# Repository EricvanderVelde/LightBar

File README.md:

# LightBar
N-Scale model train internal lighting

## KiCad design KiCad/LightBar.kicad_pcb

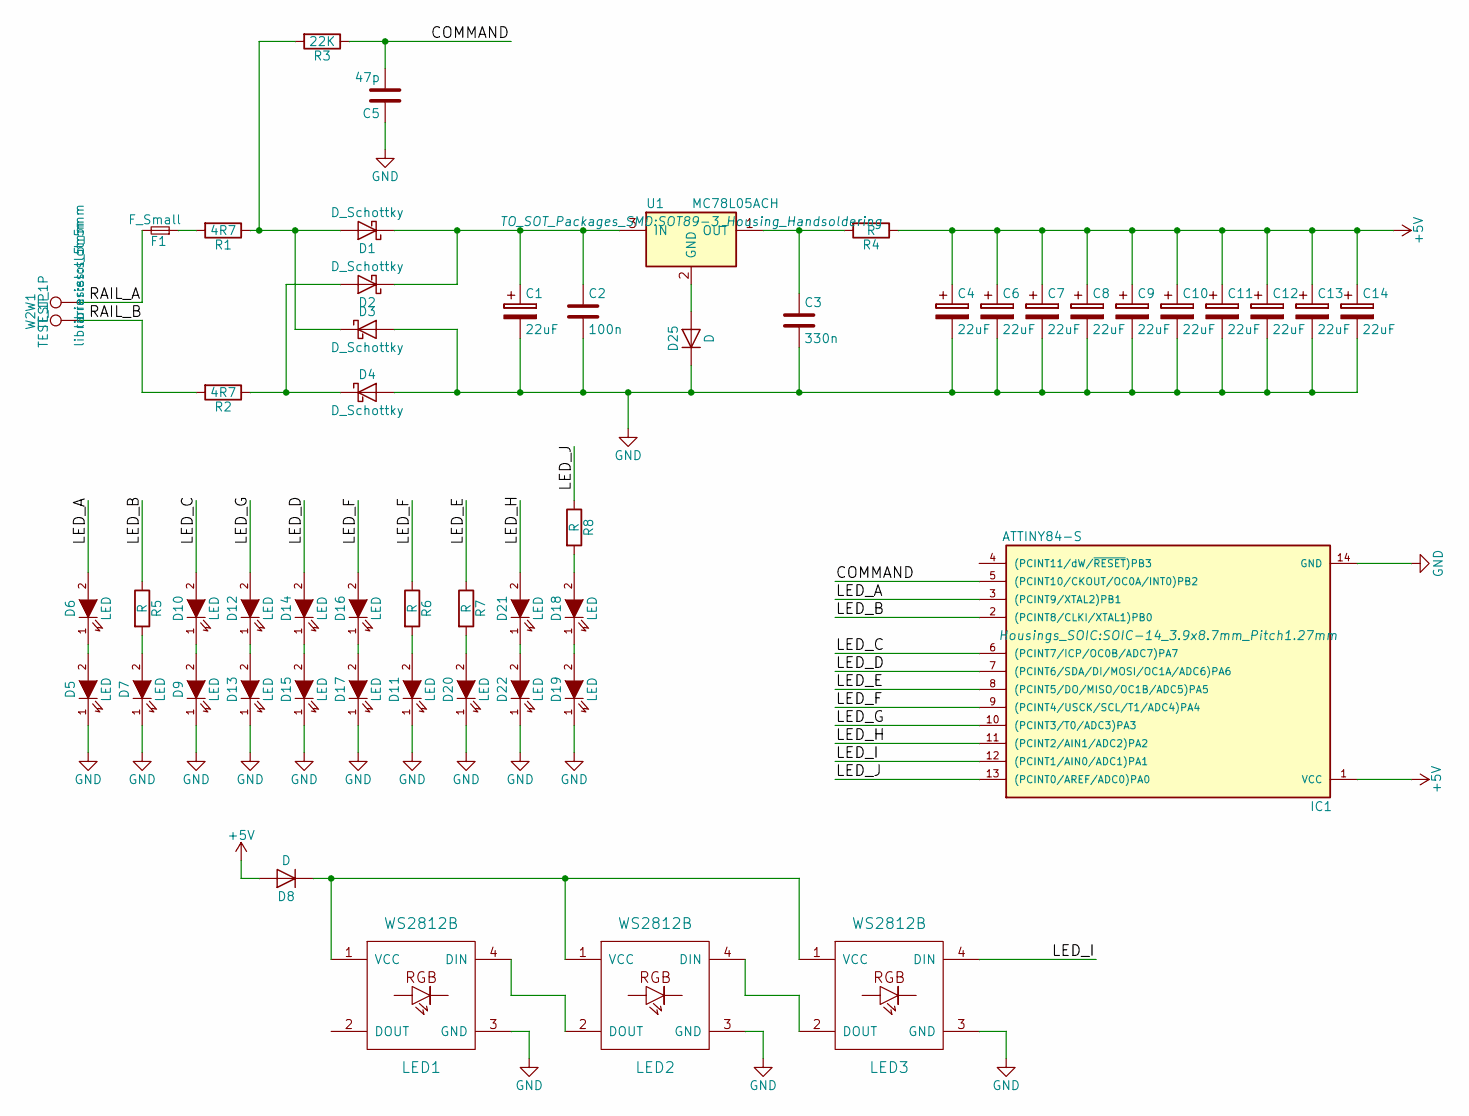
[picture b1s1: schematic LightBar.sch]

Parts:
C1, C4, C6, C7, C8, C9, C10, C11, C12, C13, C14: 22uF; TantalC_SizeB_EIA-3528_HandSoldering
C2: 100n; C_0805_HandSoldering
C3: 330n; C_0805_HandSoldering
C5: 47p; C_0805_HandSoldering
D1, D2, D3, D4: D_Schottky; SOD-323
D5, D6, D7, D9, D10, D11, D12, D13, D14, D15, D16, D17, D18, D19, D20, D21, D22: LED; LED_0805
D8, D25: D; SOD-323
F1: F_Small; R_0805_HandSoldering
IC1: ATTINY84-S; SOIC-14_3.9x8.7mm_Pitch1.27mm
LED1, LED2, LED3: WS2812B
R1, R2: 4R7; R_0805_HandSoldering
R3: 22K; R_0805_HandSoldering
R4, R5, R6, R7, R8: R; R_0805_HandSoldering
U1: MC78L05ACH; SOT89-3_Housing_Handsoldering
W1, W2: TEST_1P; slot_5mm

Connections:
+5V: C4.1, C6.1, C7.1, C8.1, C9.1, C10.1, C11.1, C12.1, C13.1, C14.1, D8.2 (A), IC1.1 (VCC), R4.1
/COMMAND: C5.2, IC1.5 ((PCINT10/CKOUT/OC0A/INT0)PB2), R3.1
/LED_A: D6.2 (A), IC1.3 ((PCINT9/XTAL2)PB1)
/LED_B: IC1.2 ((PCINT8/CLKI/XTAL1)PB0), R5.1
/LED_C: D10.2 (A), IC1.6 ((PCINT7/ICP/OC0B/ADC7)PA7)
/LED_D: D14.2 (A), IC1.7 ((PCINT6/SDA/DI/MOSI/OC1A/ADC6)PA6)
/LED_E: IC1.8 ((PCINT5/DO/MISO/OC1B/ADC5)PA5), R7.1
/LED_F: D16.2 (A), IC1.9 ((PCINT4/USCK/SCL/T1/ADC4)PA4), R6.1
/LED_G: D12.2 (A), IC1.10 ((PCINT3/T0/ADC3)PA3)
/LED_H: D21.2 (A), IC1.11 ((PCINT2/AIN1/ADC2)PA2)
/LED_I: IC1.12 ((PCINT1/AIN0/ADC1)PA1), LED3.4 (DIN)
/LED_J: IC1.13 ((PCINT0/AREF/ADC0)PA0), R8.1
/RAIL_A: F1.2, W1.1
/RAIL_B: R2.2, W2.1
GND: C1.2, C2.2, C3.2, C4.2, C5.1, C6.2, C7.2, C8.2, C9.2, C10.2, C11.2, C12.2, C13.2, C14.2, D3.2 (A), D4.2 (A), D5.1 (K), D7.1 (K), D9.1 (K), D11.1 (K), D13.1 (K), D15.1 (K), D17.1 (K), D19.1 (K), D20.1 (K), D22.1 (K), D25.1 (K), IC1.14 (GND), LED1.3 (GND), LED2.3 (GND), LED3.3 (GND)
unnamed: C1.1, C2.1, D1.1 (K), D2.1 (K), U1.3 (IN)
unnamed: C3.1, R4.2, U1.1 (OUT)
unnamed: D1.2 (A), D3.1 (K), R1.1, R3.2
unnamed: D2.2 (A), D4.1 (K), R2.1
unnamed: D5.2 (A), D6.1 (K)
unnamed: D7.2 (A), R5.2
unnamed: D8.1 (K), LED1.1 (VCC), LED2.1 (VCC), LED3.1 (VCC)
unnamed: D9.2 (A), D10.1 (K)
unnamed: D11.2 (A), R6.2
unnamed: D12.1 (K), D13.2 (A)
unnamed: D14.1 (K), D15.2 (A)
unnamed: D16.1 (K), D17.2 (A)
unnamed: D18.1 (K), D19.2 (A)
unnamed: D18.2 (A), R8.2
unnamed: D20.2 (A), R7.2
unnamed: D21.1 (K), D22.2 (A)
unnamed: D25.2 (A), U1.2 (GND)
unnamed: F1.1, R1.2
unnamed: LED1.4 (DIN), LED2.2 (DOUT)
unnamed: LED2.4 (DIN), LED3.2 (DOUT)

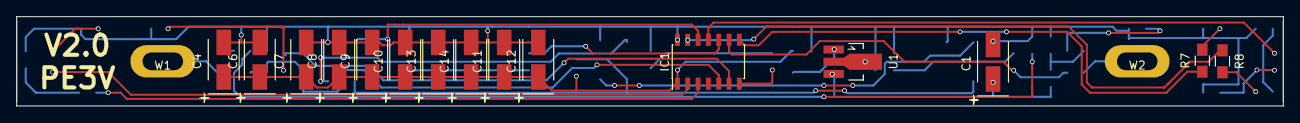
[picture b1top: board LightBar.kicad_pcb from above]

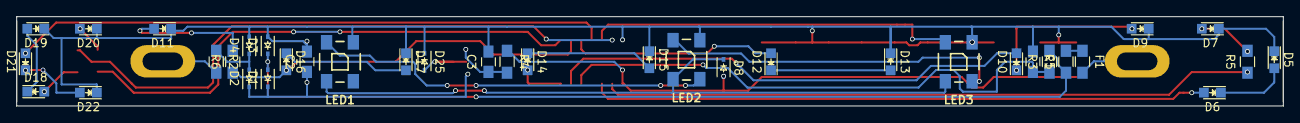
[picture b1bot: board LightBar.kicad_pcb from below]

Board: 2 copper layers, 156.0 x 11.0 mm, 53 parts (36 on the bottom side), 35 nets.
